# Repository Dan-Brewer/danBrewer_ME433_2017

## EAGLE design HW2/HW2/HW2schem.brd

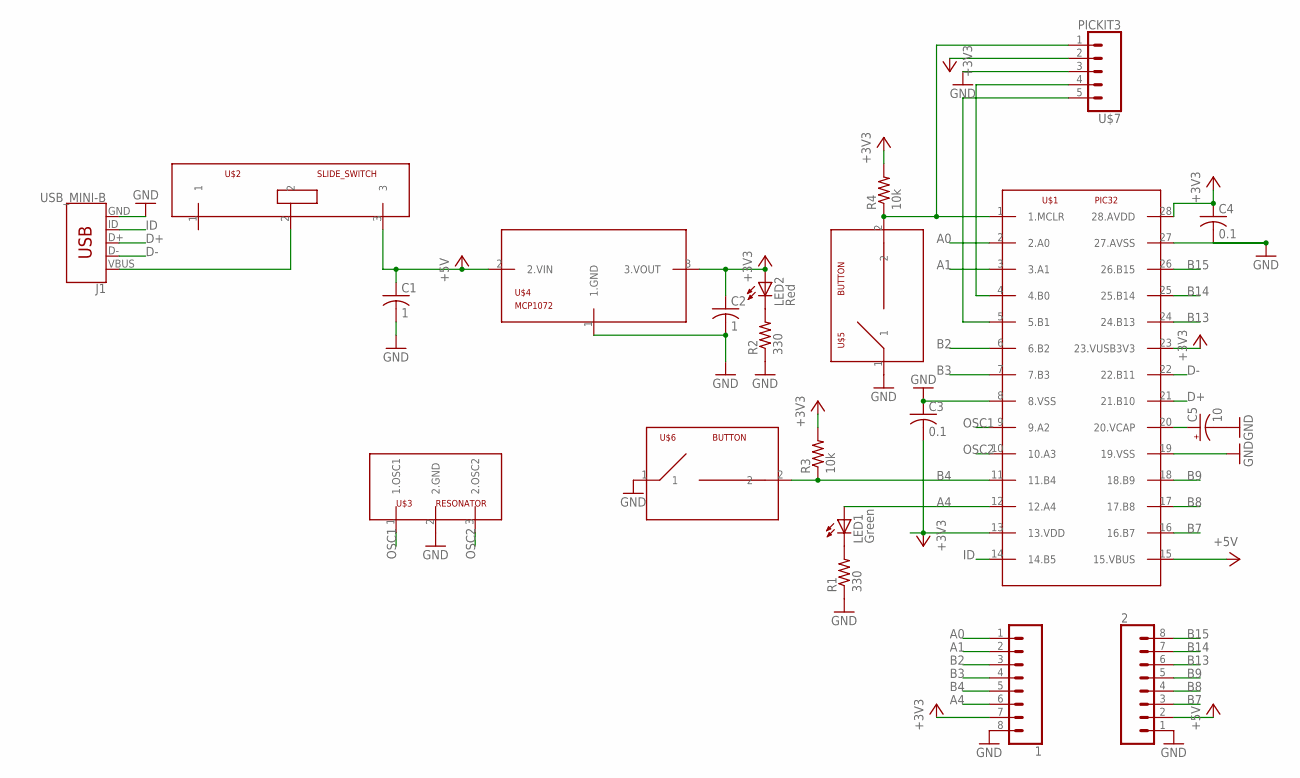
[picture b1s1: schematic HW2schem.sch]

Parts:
1, 2: CONN_08NO_SILK_FEMALE_PTH; 1X08_NO_SILK
C1, C2: 1; C025-024X044
C3, C4: 0.1; C025-024X044
C5: 10; B45181A
J1: USB_MINI-B; USB-MB-H
LED1: Green; LED3MM
LED2: Red; LED3MM
R1, R2: 330; 0204/7
R3, R4: 10k; 0204/7
U$1: PIC32; DIL28-3
U$2: SLIDE_SWITCH
U$3: RESONATOR
U$4: MCP1072; TO92
U$5, U$6: BUTTON
U$7: PICKIT3

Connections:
+3V3: 1.7, C2.1, C3.2, C4.1, LED2.A, R3.2, R4.2, U$1.13 (13.VDD), U$1.23 (23.VUSB3V3), U$1.28 (28.AVDD), U$4.3 (3.VOUT), U$7.2 (4.B0)
+5V: 2.2, C1.1, U$1.15 (15.VBUS), U$2.3, U$4.2 (2.VIN)
A0: 1.1, U$1.2 (2.A0)
A1: 1.2, U$1.3 (3.A1)
A4: 1.6, LED1.A, U$1.12 (12.A4)
B2: 1.3, U$1.6 (6.B2)
B3: 1.4, U$1.7 (7.B3)
B4: 1.5, R3.1, U$1.11 (11.B4), U$6.2
B7: 2.3, U$1.16 (16.B7)
B8: 2.4, U$1.17 (17.B8)
B9: 2.5, U$1.18 (18.B9)
B13: 2.6, U$1.24 (24.B13)
B14: 2.7, U$1.25 (25.B14)
B15: 2.8, U$1.26 (26.B15)
D+: J1.D+, U$1.21 (21.B10)
D-: J1.D-, U$1.22 (22.B11)
GND: 1.8, 2.1, C1.2, C2.2, C3.1, C4.2, C5.-, J1.GND, R1.1, R2.1, U$1.8 (8.VSS), U$1.19 (19.VSS), U$1.27 (27.AVSS), U$3.2 (2.GND), U$4.1 (1.GND), U$5.1, U$6.1, U$7.3 (3.GND)
ID: J1.ID, U$1.14 (14.B5)
unnamed: LED2.K (C), R2.2
unnamed: R4.1, U$1.1 (1.MCLR), U$5.2, U$7.1 (5.B1)
unnamed: C5.+, U$1.20 (20.VCAP)
unnamed: LED1.K (C), R1.2
unnamed: J1.VBUS, U$2.2
unnamed: U$1.4 (4.B0), U$7.4 (2.VDD)
unnamed: U$1.5 (5.B1), U$7.5 (1.MCLR)
OSC1: U$1.9 (9.A2), U$3.1 (1.OSC1)
OSC2: U$1.10 (10.A3), U$3.3 (2.OSC2)

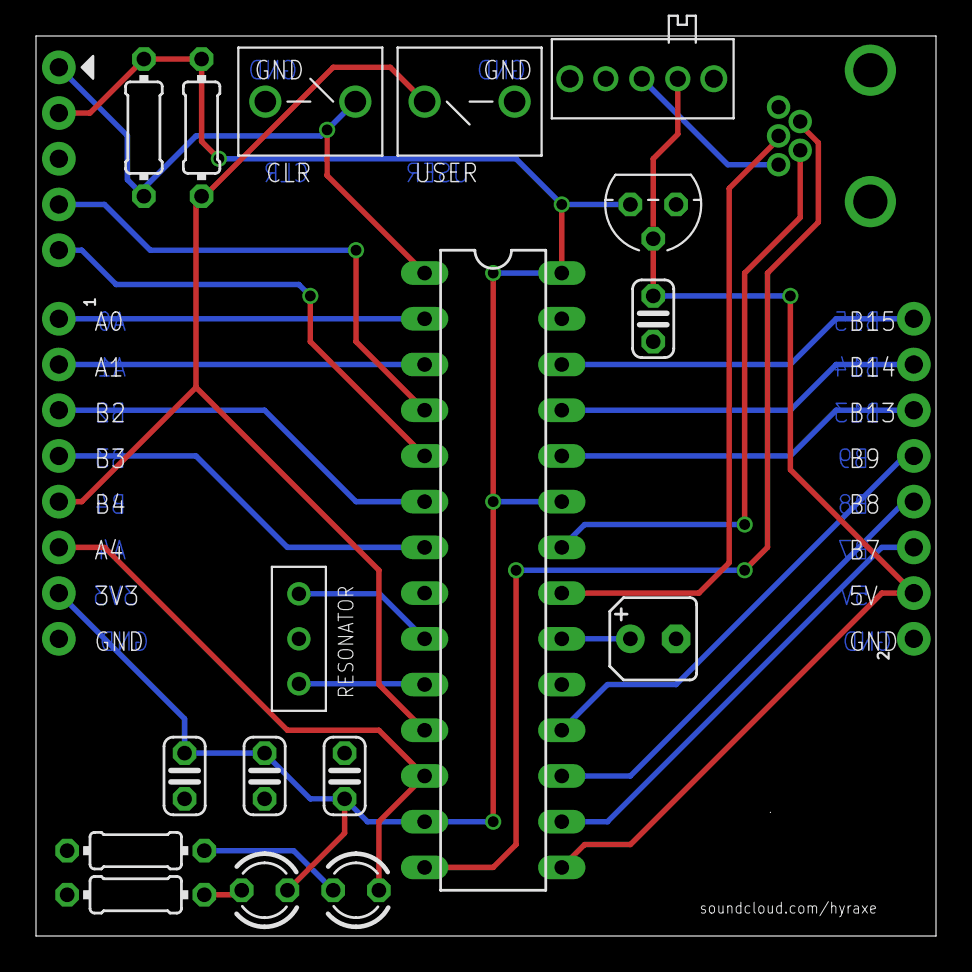
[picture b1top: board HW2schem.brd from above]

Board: 2 copper layers, 50.0 x 50.0 mm, 21 parts (0 on the bottom side), 27 nets.

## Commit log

2017-03-28 :space_invader: Added .gitattributes & .gitignore files
2017-03-28 Created readme
2017-03-28 Added university descriptor
2017-03-28 Added circuit diagram
2017-03-28 Added nScope screenshots and breadboard picture
2017-03-28 Started Programming
    LED now turns on
2017-03-28 LED pulses correctly
2017-03-28 Completed working program
2017-03-30 Created/populated library, created schematic
2017-03-31 Finished first draft of schematic
    Some hand-wavey placeholders for the switch and potentially the M08s
2017-03-31 Stuck all parts on schematic, seems a bit messy
2017-04-03 Updated Library and schematic based on released video
2017-04-03 Rearranged board
2017-04-04 Finished tentative board, added sick logo
2017-04-06 Completed board, generated gerber files
2017-04-06 Created circuit diagram for hw4
2017-04-07 Started Program
2017-04-07 Code builds successfully, but A and B always low
2017-04-07 Debugged Program, think it works properly now
2017-04-07 Finished debugging program, uploaded screenshot
2017-04-11 Created HW5 folder, added circuit diagram
2017-04-12 Program is buggy, but draft is complete
2017-04-12 Finished debugging program, added updated circuit diagram
2017-04-13 Created HW6 Folder, got string to print on LCD
2017-04-14 Finished program
2017-04-18 Created HW7
2017-04-18 Who am I read not working currently
2017-04-18 Data reads properly from accelerometer
2017-04-18 Completed program
2017-04-20 Created and finished hw8
2017-04-25 Created HW9, computer recognizes pic
2017-04-25 Completed HW9
2017-04-29 HW10 now same as HW9 code to start
2017-04-29 Got pic to read into matlab, and IIR working
2017-04-29 Implemented moving average filter
2017-04-29 Hw10 program finished, gains selected
2017-04-29 Added figures and matlab client
2017-05-02 Added and finished HW11
2017-05-04 Added and finished HW12
2017-05-09 Finished HW13
2017-05-11 Started HW14
    Potential bug in PIC code when sent numbers are too large (over 5
    digits)
2017-05-11 Added Android App
2017-05-11 Completed HW14
2017-05-16 Added DXF and STL files for laser cutting/3d printing
2017-05-17 Edited wheel to fit requirements
2017-05-18 Modified dxfs to meet requirements, added pictures for HW16
2017-05-18 Separated folders for 3d print and laser cut
2017-06-07 Got robot to follow line, using MCTest PIC code in HW18 and IP android code in HW13
2017-06-07 Added code in proper HW18,19,20 folders
